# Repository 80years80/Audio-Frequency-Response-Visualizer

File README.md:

# Audio-Frequency-Response-Visualizer
Done on Arduino Uno, WS2812B LED lights, Shield PCB for Arduino Designed in Eagle

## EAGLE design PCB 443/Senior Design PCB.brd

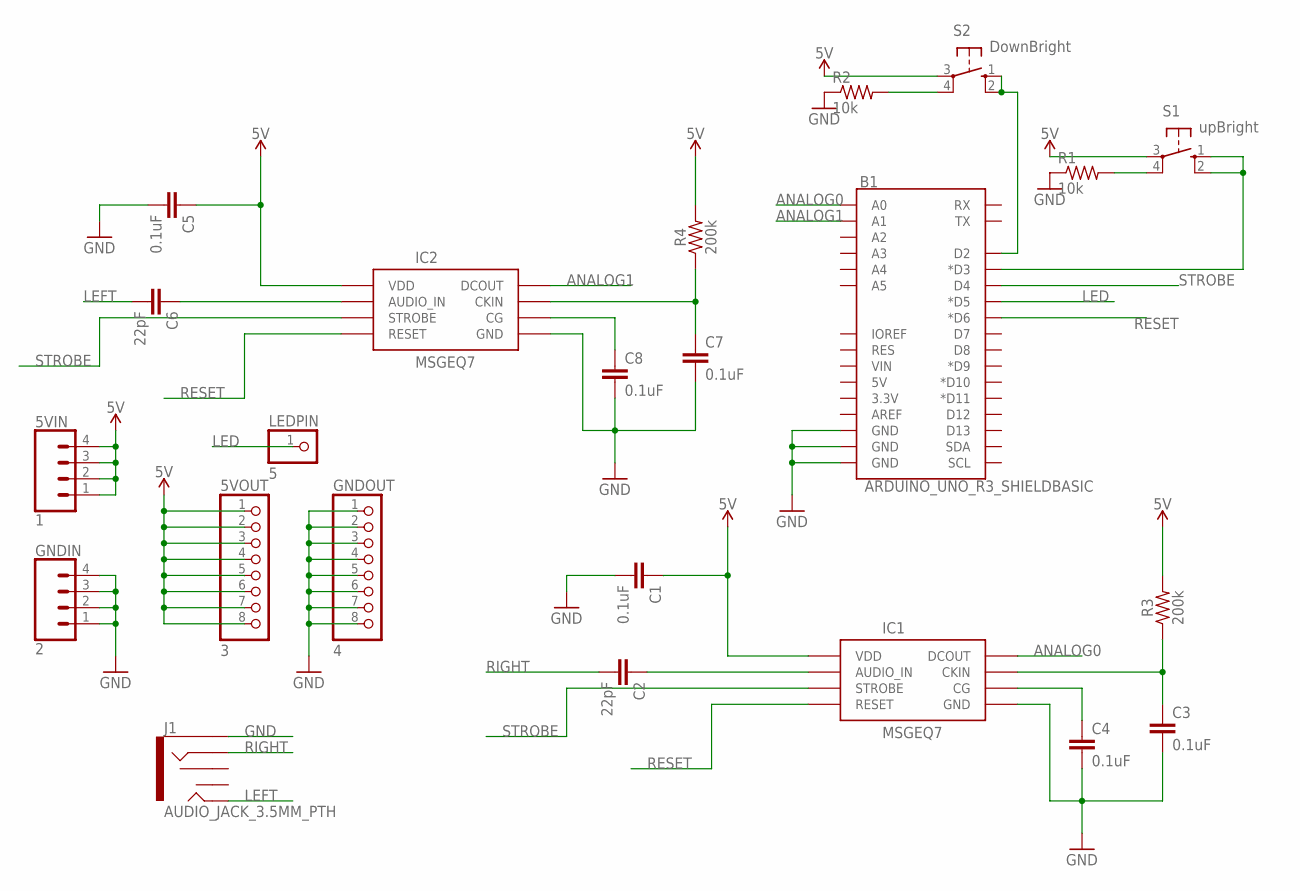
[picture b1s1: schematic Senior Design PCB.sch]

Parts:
5VIN: 1; 1X04
5VOUT: 3; 1X08-BIG
B1: ARDUINO_UNO_R3_SHIELDBASIC; UNO_R3_SHIELD
C1, C3, C4, C5, C7, C8: 0.1uF; CAP-PTH-SMALL-KIT
C2, C6: 22pF; CAP-PTH-2.54
GNDIN: 2; 1X04
GNDOUT: 4; 1X08-BIG
IC1, IC2: MSGEQ7P; DIP08
J1: AUDIO_JACK_3.5MM_PTH; AUDIO-JACK
LEDPIN: 5; 1X01
R1, R2: 10k; 0204/7
R3, R4: 200k; AXIAL-0.3
S1: upBright; B3F-40XX
S2: DownBright; B3F-40XX

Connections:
5V: 5VIN.1, 5VIN.2, 5VIN.3, 5VIN.4, 5VOUT.1, 5VOUT.2, 5VOUT.3, 5VOUT.4, 5VOUT.5, 5VOUT.6, 5VOUT.7, 5VOUT.8, C1.1, C5.1, IC1.1 (VDD), IC2.1 (VDD), R3.P$2 (2), R4.P$2 (2), S1.3, S2.3
ANALOG0: B1.A0, IC1.3 (DCOUT)
ANALOG1: B1.A1, IC2.3 (DCOUT)
GND: B1.GND@0 (GND), B1.GND@1 (GND), B1.GND@2 (GND), C1.2, C3.2, C4.2, C5.2, C7.2, C8.2, GNDIN.1, GNDIN.2, GNDIN.3, GNDIN.4, GNDOUT.1, GNDOUT.2, GNDOUT.3, GNDOUT.4, GNDOUT.5, GNDOUT.6, GNDOUT.7, GNDOUT.8, IC1.2 (GND), IC2.2 (GND), J1.SLEEVE, R1.1, R2.1
LED: B1.D5 (*D5), LEDPIN.1
LEFT: C6.2, J1.TIP
unnamed: R1.2, S1.4 (P1)
unnamed: R2.2, S2.4 (P1)
unnamed: B1.D3 (*D3), S1.1 (S), S1.2 (S1)
unnamed: C2.1, IC1.5 (AUDIO_IN)
unnamed: C3.1, IC1.8 (CKIN), R3.P$1 (1)
unnamed: C4.1, IC1.6 (CG)
unnamed: C6.1, IC2.5 (AUDIO_IN)
unnamed: C7.1, IC2.8 (CKIN), R4.P$1 (1)
unnamed: C8.1, IC2.6 (CG)
unnamed: B1.D2, S2.1 (S), S2.2 (S1)
RESET: B1.D6 (*D6), IC1.7 (RESET), IC2.7 (RESET)
RIGHT: C2.2, J1.RING
STROBE: B1.D4, IC1.4 (STROBE), IC2.4 (STROBE)

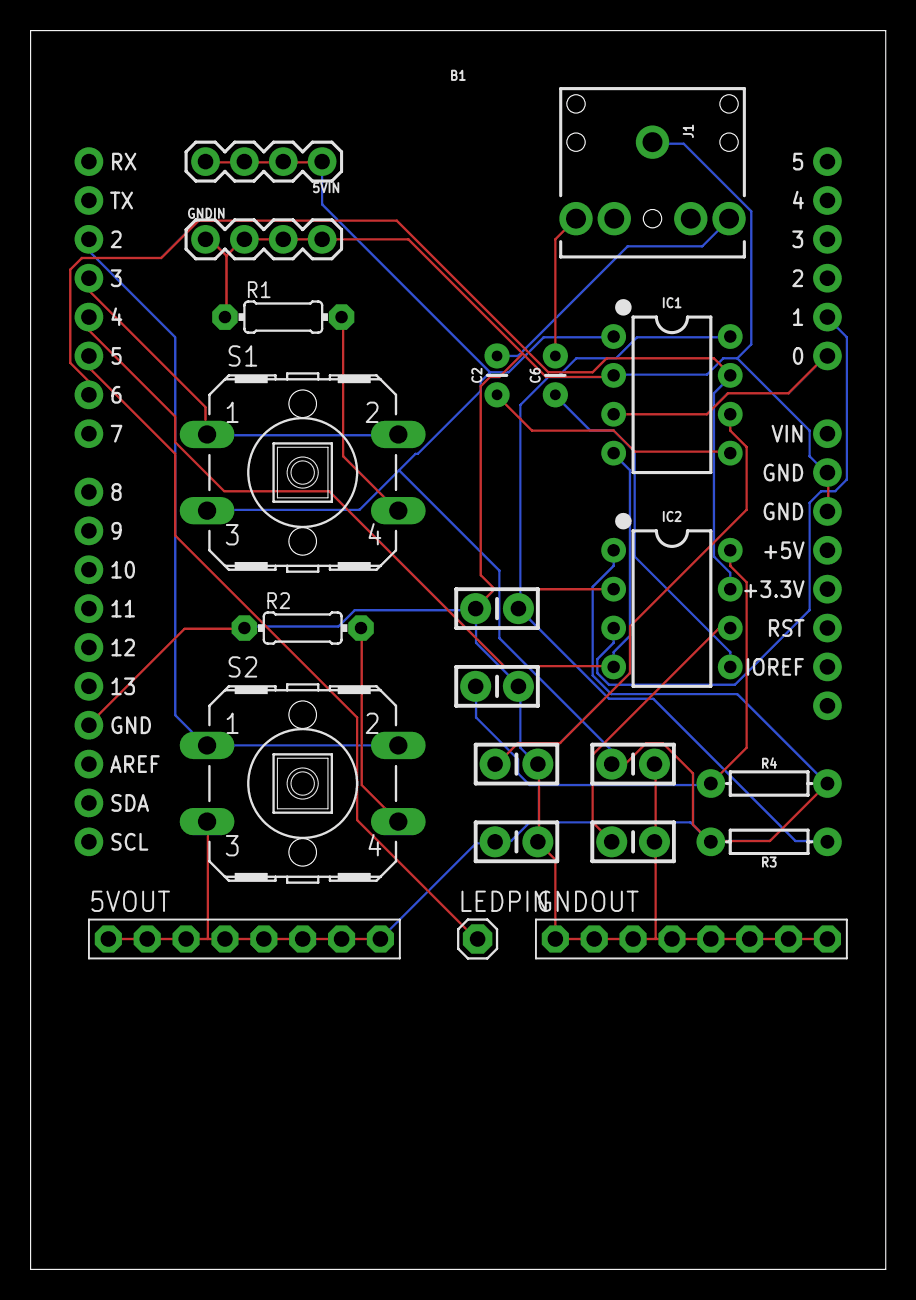
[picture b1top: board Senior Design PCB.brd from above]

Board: 2 copper layers, 55.9 x 81.0 mm, 23 parts (0 on the bottom side), 19 nets.

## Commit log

2019-07-09 Fixed code
    Added correct version of the code

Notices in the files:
parts and their libraries:
SparkFun-Connectors: Licensing: Creative Commons ShareAlike 4.0 International - https://creativecommons.org/licenses/by-sa/4.0
